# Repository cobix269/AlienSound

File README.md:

<p align="center"><strong>A hands-on audio synth project, from breadboard experiments to a custom PCB.</strong><br>By Clarisse, Raphael &amp; Zoé</p>

<p align="center"><a href="#watch--listen">Watch &amp; listen</a> · <a href="#breadboard-experiments">Breadboard gallery</a> · <a href="#kicad-design">KiCad design</a></p>

---

## The project

**AlienSound** explores electronic sound through physical circuits, adjustable controls and visible LED activity. This repository brings together photographs of the prototypes, recordings of the breadboard experiments, and the editable KiCad schematic and PCB layout.

The documentation follows the build from **breadboard exploration → soldered circuit → extended PCB version**. The breadboard media, hand-drawn schematic, TinkerCAD breadboard diagram and simulation video, soldered-build photographs, and KiCad files are available below. 

## Watch & listen

### Controls in action

<p align="center"></p>
<p align="center"><strong>Turn the controls. Observe the LEDs. Explore the recordings.</strong><br>The GIF is a silent, five-second excerpt. Open the full video for its recorded audio.</p>

| Breadboard demonstration | Control experiment | Close-up demonstration |
| :---: | :---: | :---: |
|  |  |  |
| **39.3 s** · [Watch video](media/video/F5FD7321-8B4E-42B4-98F9-2C26B623B50A.mp4) | **13.0 s** · [Watch video](media/video/IMG_2965.mp4) | **16.5 s** · [Watch video](media/video/IMG_2967.mp4) |
| [Listen / download audio](media/audio/F5FD7321-8B4E-42B4-98F9-2C26B623B50A.m4a) | [Listen / download audio](media/audio/IMG_2965.m4a) | [Listen / download audio](media/audio/IMG_2967.m4a) |

The audio files are the original AAC tracks extracted from the supplied videos, without added sound or processing. They are recordings of the surrounding scene, not calibrated electrical measurements or direct line-output recordings. If a media file does not play in the repository viewer, download it to play locally.

## Breadboard experiments

The photographs document two visible arrangements: a compact setup with a light-dependent resistor, LED and speaker, and a longer breadboard with several rotary controls. The breadboard arrangements may differ slightly from the diagrams below.

### 01 · Compact prototype

A photoresistor, illuminated LED, external potentiometer and small speaker are visible. An Arduino Mega ADK is also present in the setup; no firmware is supplied, so its exact role is not asserted here.

### 02 · Adjustable controls

The larger prototype exposes multiple potentiometers for hands-on adjustment. This photograph records the physical arrangement of the controls and wiring.

### 03 · Circuit detail

A closer view records the integrated circuit and capacitor area. Component values and connections should be read from the design files and circuit diagrams, rather than inferred from the photograph alone.

## Circuit documentation

| Document | Status | Location |
| --- | --- | --- |
| Hand-drawn circuit diagram | Included | [Hand-drawn circuit](docs/hand-drawn/Hand-drawn.jpeg) |
| TinkerCAD breadboard diagram | Included | [Breadboard diagram](docs/tinkercad/breadboard.png) |
| TinkerCAD simulation video | Included | [Watch simulation](docs/tinkercad/Tinkercad_test595.mp4) |
| KiCad schematic | Included | [Editable schematic](hardware/kicad/AlienSound.kicad_sch) · [SVG preview](docs/exports/AlienSound.svg) |

### TinkerCAD simulation

The breadboard diagram documents the simulated wiring and component arrangement.

**[▶ Watch the TinkerCAD test video](docs/tinkercad/Tinkercad_test595.mp4)**

The supplied simulation recording is separate from the recordings of the physical breadboard. Download the MP4 if it does not play in the GitHub viewer.

### Hand-drawn circuit

The drawing shows three blocks:

- **Clock and data oscillators (top right):** two 74HC14 Schmitt-trigger inverters (pins 1→2 and 3→4),
  each set up as a relaxation oscillator with a 10 kΩ potentiometer in the feedback path and a 10 µF
  capacitor to ground. One output goes to the SER input of the 74HC595, the other to its clock
  inputs (SRCLK and RCLK, tied together). OE is grounded and SRCLR is held at 5 V.
- **LED register (centre):** the 74HC595 drives LEDs to ground from its outputs. Three outputs
  are also connected through diodes to the inputs of the audio oscillators below.
- **Audio oscillators and amplifier (bottom):** three more 74HC14 inverters (pins 11→10, 13→12, 9→8),
  each again an RC oscillator with a 10 kΩ potentiometer and a 10 µF capacitor. Their outputs are mixed
  through three 1 kΩ resistors, passed through a 10 µF coupling capacitor to the LM386 (5 V supply),
  and sent to the speaker through a 220 µF capacitor.

## Soldered synth

### Assembled circuit

The component-side photograph shows the synth assembled on perfboard, with three rotary controls and a row of LEDs.

### Powered setup

Several LEDs are illuminated while a control is being adjusted.

## KiCad design

### Editable source files

- [AlienSound.kicad_pro](hardware/kicad/AlienSound.kicad_pro) — KiCad project.
- [AlienSound.kicad_sch](hardware/kicad/AlienSound.kicad_sch) — schematic, including embedded symbols.
- [AlienSound.kicad_pcb](hardware/kicad/AlienSound.kicad_pcb) — placed components, copper routing and board outline.
- [Component inventory](hardware/bom.csv) — references, values and footprints exported from the supplied schematic.

The files were created with **KiCad 10.0** and the previews were exported using **KiCad CLI 10.0.6**. Open the `.kicad_pro` file in KiCad 10 or a compatible later version, then launch the schematic or PCB editor.

### Schematic

The source design contains three main ICs:

| Reference | Component | Position in the design |
| --- | --- | --- |
| U2 | 74HC14 | Several inverter sections connected to resistor/capacitor networks and the adjustable branches |
| U1 | 74HC595 | Eight outputs connected to LEDs; three also connect through diodes to adjustable branches |
| U3 | LM386 | Audio-stage IC, with output connected through C7 to the speaker connector LS1 |

This is a structural reading of the supplied schematic, not a statement that every connection has been electrically validated. The [design notes](docs/design-notes.md) record specific points to review before fabrication.

### 3D board previews

These KiCad 3D views show the component placement and overall appearance of the designed PCB.

**Top view**

**Perspective view**

### Physical layout

| Property | Supplied PCB |
| --- | --- |
| Board outline | **70 × 50 mm**, measured between the Edge.Cuts centre lines |
| Nominal thickness | **1.6 mm** |
| Copper layers | **2** — F.Cu and B.Cu |
| Footprints | **30** |
| IC packages | DIP-16, DIP-14 and DIP-8, each with 7.62 mm row spacing |
| Controls | Three Bourns 3296W vertical trimmer footprints |
| Speaker connection | Two-pin header, 2.54 mm pitch |

The layout uses real component footprints. The trimmer footprints in the PCB are different from the large rotary potentiometers visible in the breadboard photos; the final component choice and mechanical fit therefore need confirmation.

## Repository map

```text
AlienSound/
├── README.md
├── hardware/
│   ├── kicad/          Editable project, schematic and PCB
│   └── bom.csv         Component inventory from the schematic
├── media/
│   ├── photos/         Three breadboard photographs
│   ├── video/          Full demonstrations with their audio
│   ├── audio/          Audio-only versions of the recordings
│   └── previews/       Video stills and animated excerpt
└── docs/
    ├── exports/        KiCad schematic, PCB preview and title graphic
    ├── hand-drawn/     Hand-drawn circuit documentation
    ├── soldered/       Assembly photographs and operating proof
    ├── tinkercad/      Breadboard diagram and simulation video
    └── design-notes.md
```

---

*AlienSound — Making our own musical instrument. Project credits follow the supplied KiCad title block: Clarisse / Raphael / Zoé.*

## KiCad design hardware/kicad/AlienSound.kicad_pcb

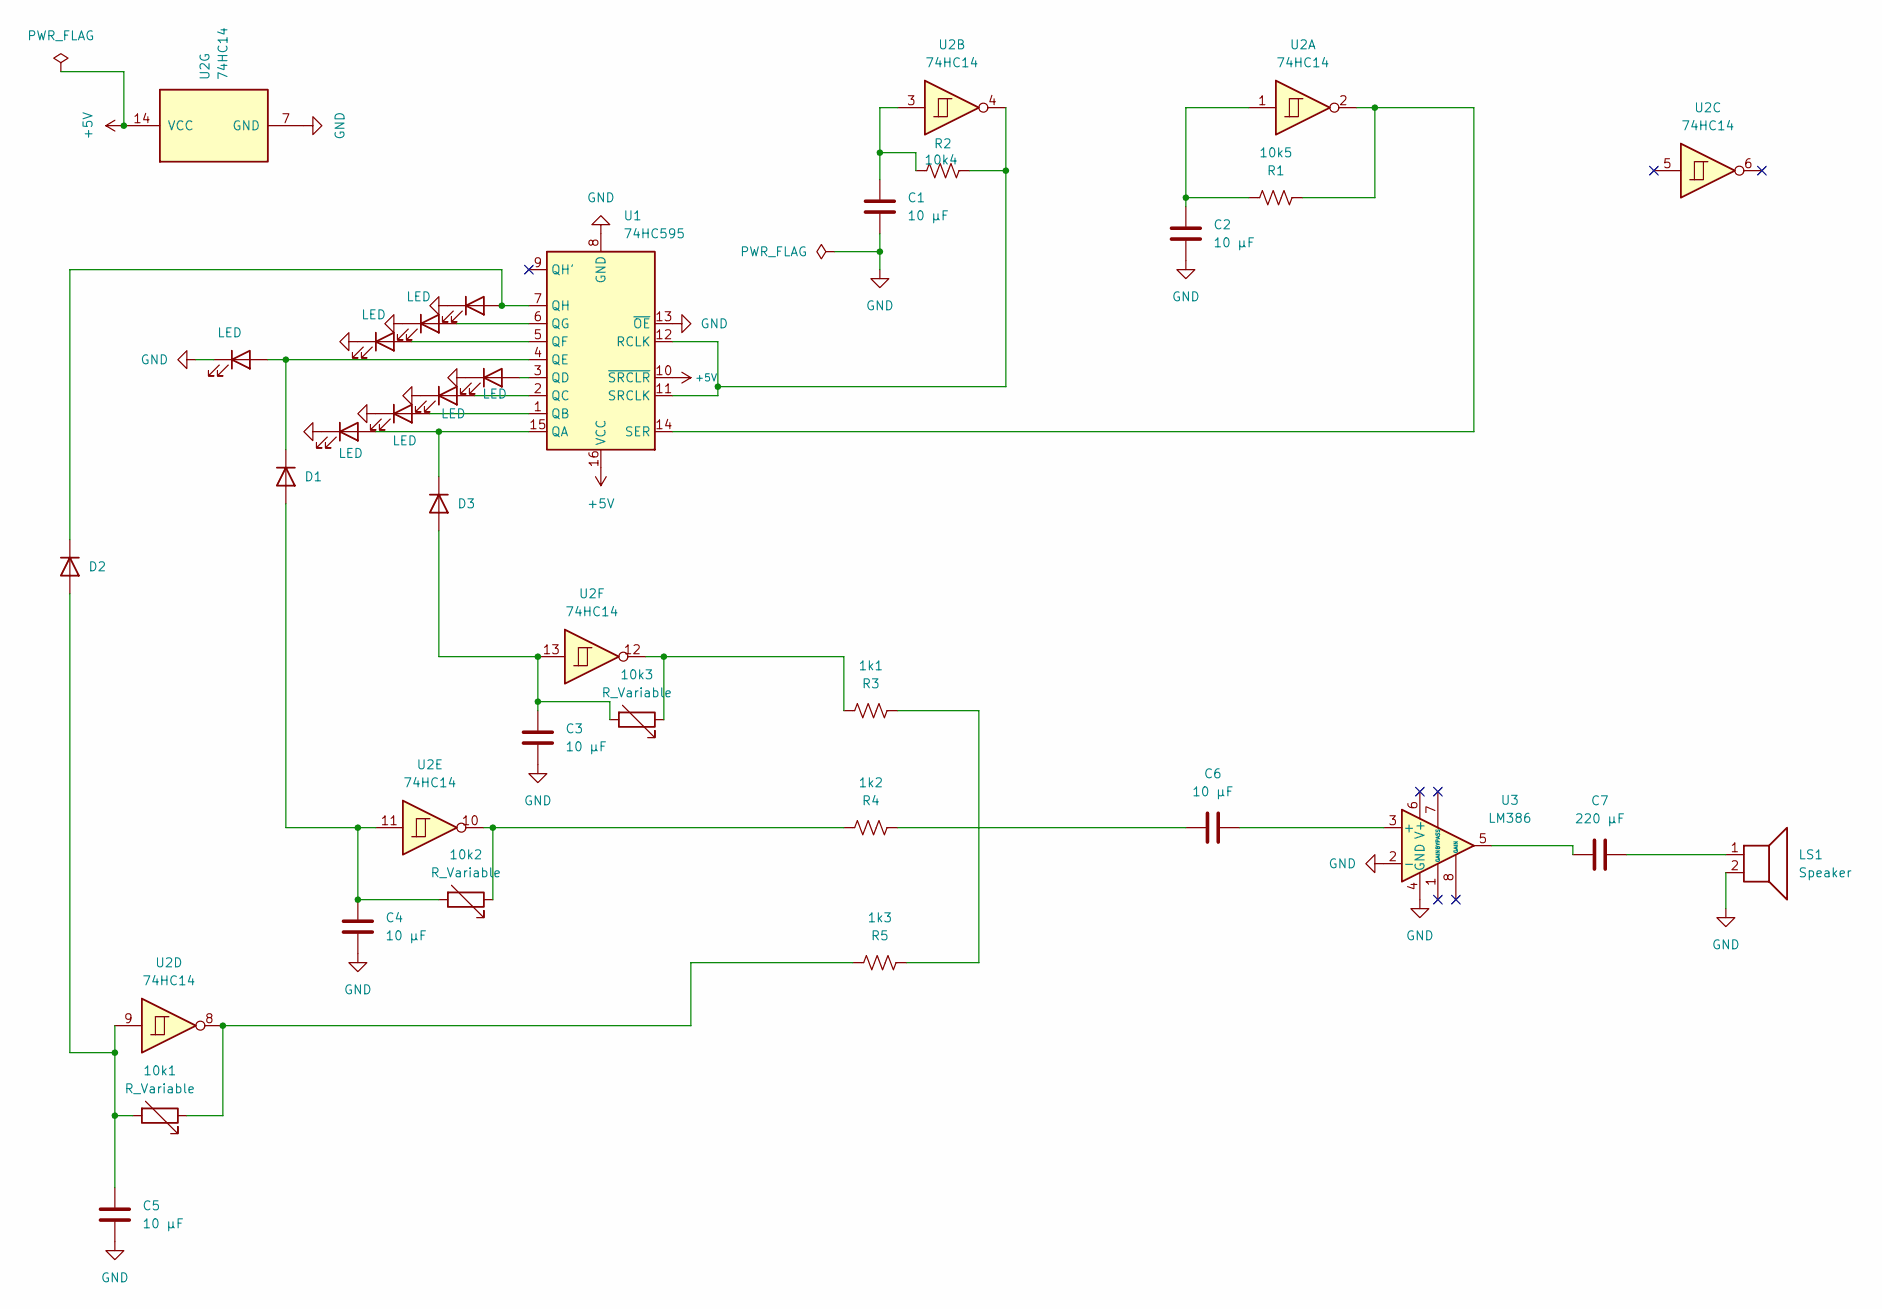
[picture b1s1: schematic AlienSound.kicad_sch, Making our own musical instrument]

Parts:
1k1: R3; R_Axial_DIN0207_L6.3mm_D2.5mm_P7.62mm_Horizontal
1k2: R4; R_Axial_DIN0207_L6.3mm_D2.5mm_P7.62mm_Horizontal
1k3: R5; R_Axial_DIN0207_L6.3mm_D2.5mm_P7.62mm_Horizontal
10k1, 10k2, 10k3: R_Variable; Potentiometer_Bourns_3296W_Vertical
10k4: R2; R_Axial_DIN0207_L6.3mm_D2.5mm_P7.62mm_Horizontal
10k5: R1; R_Axial_DIN0207_L6.3mm_D2.5mm_P7.62mm_Horizontal
C1, C2, C3, C4, C5, C6: 10 µF; C_Radial_D5.0mm_H11.0mm_P2.00mm
C7: 220 µF; C_Radial_D5.0mm_H11.0mm_P2.00mm
D1: D2; D_DO-35_SOD27_P7.62mm_Horizontal
D2, D4, D5, D6, D7, D9, D10, D11: LED; LED_D5.0mm
D3: D1; D_DO-35_SOD27_P7.62mm_Horizontal
D8: D3; D_DO-35_SOD27_P7.62mm_Horizontal
LS1: Speaker; PinHeader_1x02_P2.54mm_Vertical
U1: 74HC595; DIP-16_W7.62mm
U2: 74HC14; DIP-14_W7.62mm
U3: LM386; DIP-8_W7.62mm

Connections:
+5V: U1.10 (~SRCLR), U1.16 (VCC), U2.14 (VCC)
GND: C1.2, C2.2, C3.2, C4.2, C5.2, D2.1 (K), D4.1 (K), D5.1 (K), D6.1 (K), D7.1 (K), D9.1 (K), D10.1 (K), D11.1 (K), LS1.2, U1.8 (GND), U1.13 (~OE), U2.7 (GND), U3.2 (-), U3.4 (GND)
unnamed: 1k1.2, 1k3.2
unnamed: 1k2.2, C6.2
unnamed: 1k3.1, 10k1.1, U2.8
unnamed: 1k2.1, 10k2.1, U2.10
unnamed: 1k1.1, 10k3.1, U2.12
unnamed: 10k4.1, C1.1, U2.3
unnamed: 10k5.1, C2.1, U2.1
unnamed: C7.1, LS1.1
unnamed: C7.2, U3.5
unnamed: 10k1.2, C5.1, D1.2 (A), U2.9
unnamed: D1.1 (K), D10.2 (A), U1.7 (QH)
unnamed: D2.2 (A), D3.1 (K), U1.4 (QE)
unnamed: 10k2.2, C4.1, D3.2 (A), U2.11
unnamed: D4.2 (A), D8.1 (K), U1.15 (QA)
unnamed: D5.2 (A), U1.5 (QF)
unnamed: D6.2 (A), U1.1 (QB)
unnamed: D7.2 (A), U1.6 (QG)
unnamed: 10k3.2, C3.1, D8.2 (A), U2.13
unnamed: D9.2 (A), U1.2 (QC)
unnamed: D11.2 (A), U1.3 (QD)
unnamed: 10k4.2, U1.11 (SRCLK), U1.12 (RCLK), U2.4
unnamed: 10k5.2, U1.14 (SER), U2.2
unnamed: C6.1, U3.3 (+)

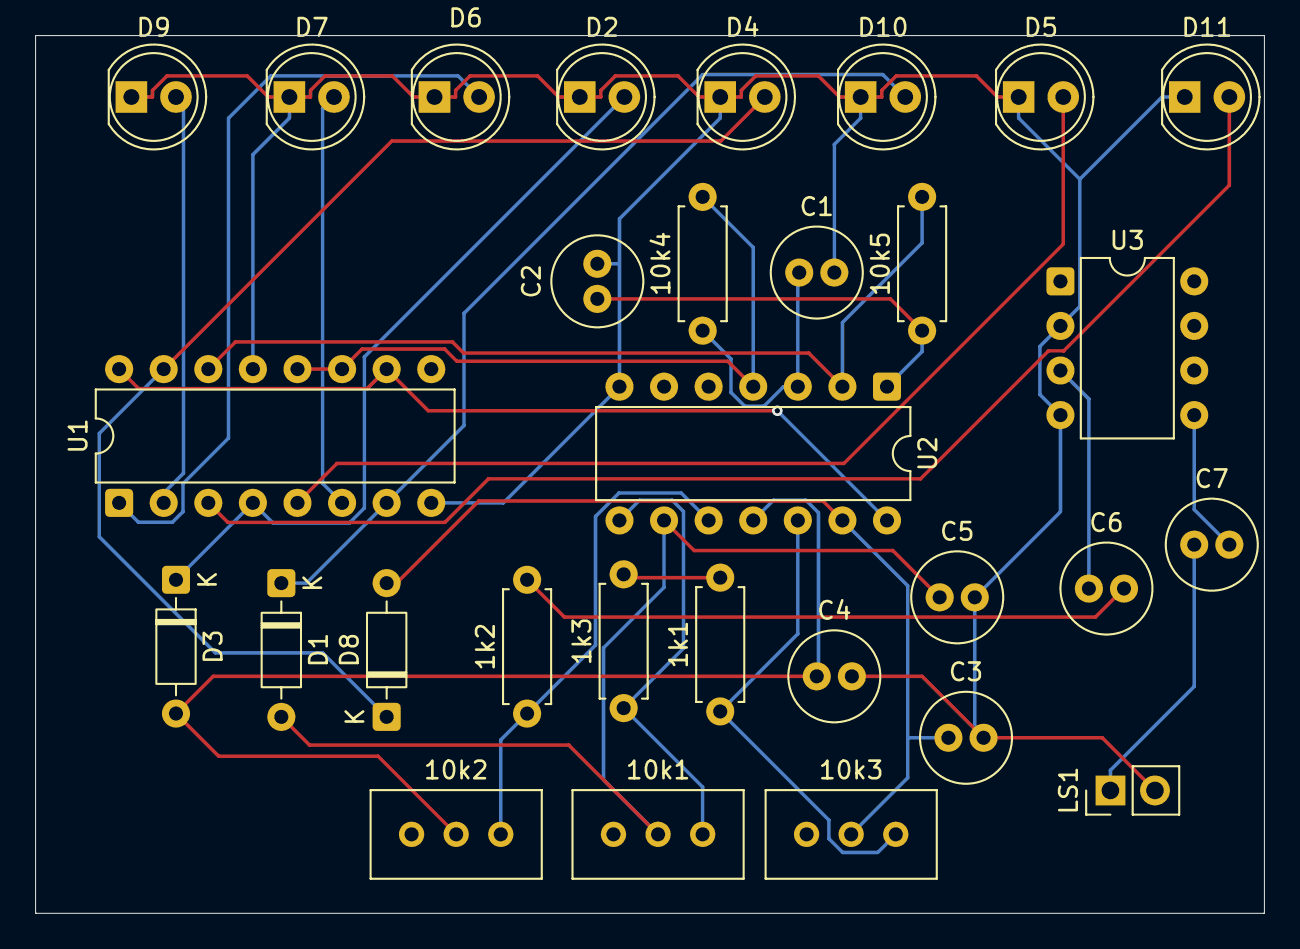
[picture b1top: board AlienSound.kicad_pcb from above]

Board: 2 copper layers, 70.0 x 50.0 mm, 30 parts (0 on the bottom side), 25 nets.
